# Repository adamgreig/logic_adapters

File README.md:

# Adapter PCBs for Saleae Logic

## PMOD + Picoblade

Connects a Saleae Logic or other logic analyser to a double-PMOD socket header
and to two Picoblade connectors, one 4-pin and one 7-pin.

## Cortex Debug

Connects a Saleae Logic or other logic analyser to two Cortex Debug 2x5 0.05"
connectors which are connected together, allowing analysis of signals between
a debugger and a target.

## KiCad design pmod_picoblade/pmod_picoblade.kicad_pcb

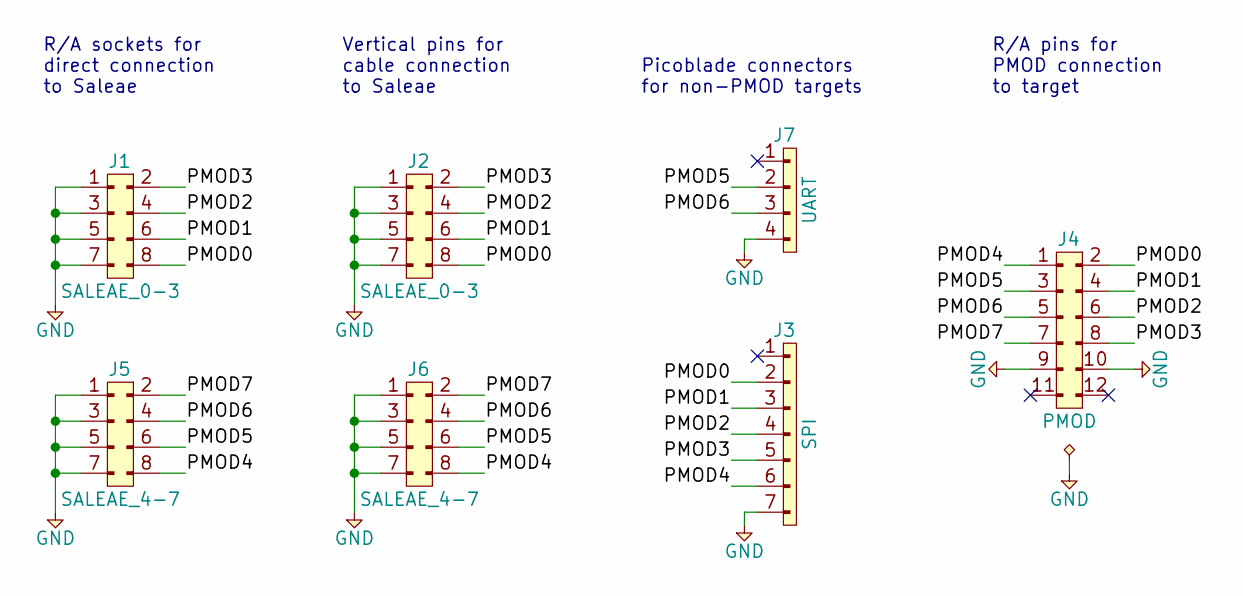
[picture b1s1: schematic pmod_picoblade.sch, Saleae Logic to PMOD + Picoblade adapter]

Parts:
J1: SALEAE_0-3; DIL-254P-08; Farnell 1668343
J2: SALEAE_0-3; DIL-254P-08; Farnell 2856692
J3: SPI; MOLEX-PICOBLADE-53398-0771; Farnell 9786368
J4: PMOD; DIL-254P-12; Farnell 2032721
J5: SALEAE_4-7; DIL-254P-08; Farnell 1668343
J6: SALEAE_4-7; DIL-254P-08; Farnell 2856692
J7: UART; MOLEX-PICOBLADE-53398-0471; Farnell 1125367

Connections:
/PMOD0: J1.8, J2.8, J3.2, J4.2
/PMOD1: J1.6, J2.6, J3.3, J4.4
/PMOD2: J1.4, J2.4, J3.4, J4.6
/PMOD3: J1.2, J2.2, J3.5, J4.8
/PMOD4: J3.6, J4.1, J5.8, J6.8
/PMOD5: J4.3, J5.6, J6.6, J7.2
/PMOD6: J4.5, J5.4, J6.4, J7.3
/PMOD7: J4.7, J5.2, J6.2
GND: J1.1, J1.3, J1.5, J1.7, J2.1, J2.3, J2.5, J2.7, J3.7, J4.9, J4.10, J5.1, J5.3, J5.5, J5.7, J6.1, J6.3, J6.5, J6.7, J7.4

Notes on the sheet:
R/A sockets for direct connection to Saleae
Vertical pins for cable connection to Saleae
Picoblade connectors for non-PMOD targets
R/A pins for PMOD connection to target

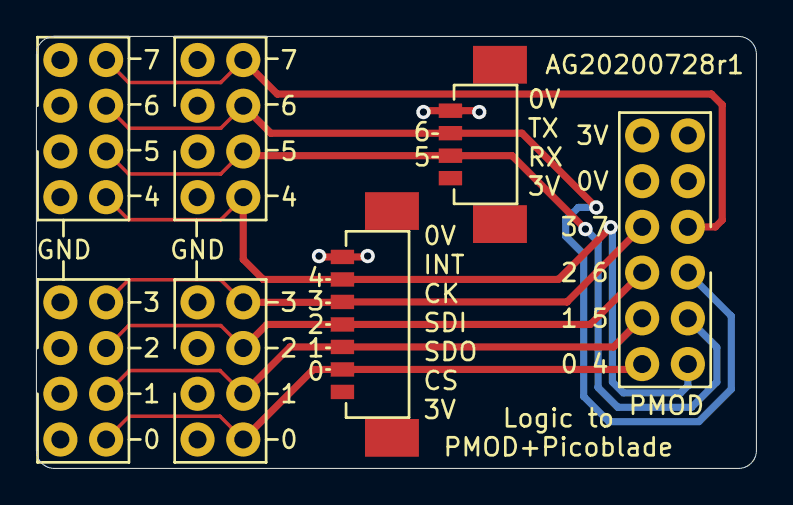
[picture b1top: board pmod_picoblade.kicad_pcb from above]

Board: 2 copper layers, 40.0 x 24.0 mm, 7 parts (0 on the bottom side), 9 nets.

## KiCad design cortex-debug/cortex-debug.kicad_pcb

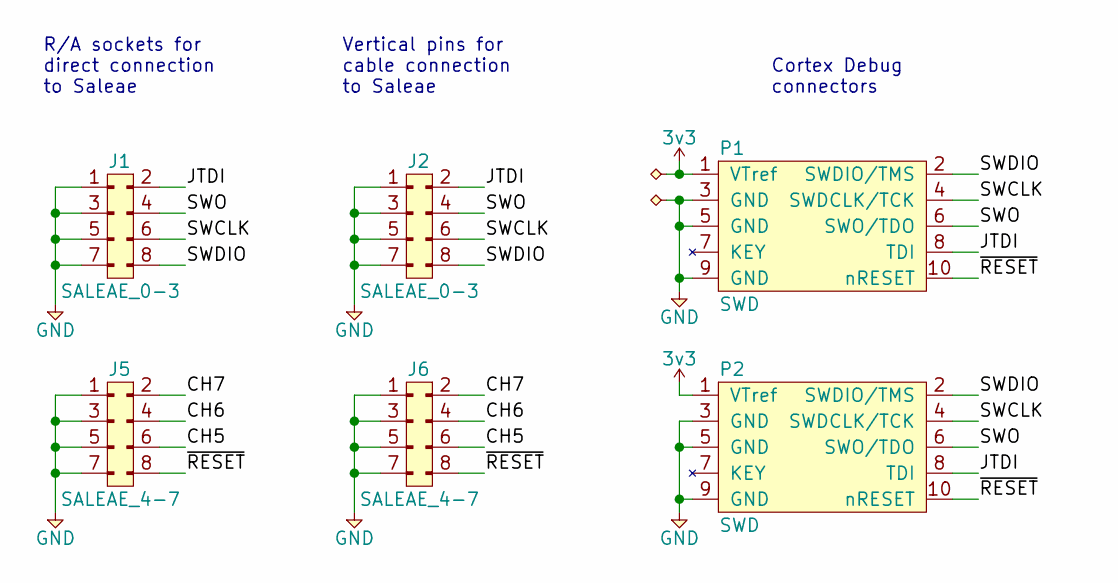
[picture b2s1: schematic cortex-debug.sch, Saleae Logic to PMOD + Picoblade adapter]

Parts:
J1: SALEAE_0-3; DIL-254P-08; Farnell 1668343
J2: SALEAE_0-3; DIL-254P-08; Farnell 2856692
J5: SALEAE_4-7; DIL-254P-08; Farnell 1668343
J6: SALEAE_4-7; DIL-254P-08; Farnell 2856692
P1, P2: SWD; FTSH-105-01-L-DV-K; Farnell 2856437

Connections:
3v3: P1.1 (VTref), P2.1 (VTref)
/CH5: J5.6, J6.6
/CH6: J5.4, J6.4
/CH7: J5.2, J6.2
/JTDI: J1.2, J2.2, P1.8 (TDI), P2.8 (TDI)
/SWCLK: J1.6, J2.6, P1.4 (SWDCLK/TCK), P2.4 (SWDCLK/TCK)
/SWDIO: J1.8, J2.8, P1.2 (SWDIO/TMS), P2.2 (SWDIO/TMS)
/SWO: J1.4, J2.4, P1.6 (SWO/TDO), P2.6 (SWO/TDO)
/~RESET: J5.8, J6.8, P1.10 (nRESET), P2.10 (nRESET)
GND: J1.1, J1.3, J1.5, J1.7, J2.1, J2.3, J2.5, J2.7, J5.1, J5.3, J5.5, J5.7, J6.1, J6.3, J6.5, J6.7, P1.3 (GND), P1.5 (GND), P1.9 (GND), P2.3 (GND), P2.5 (GND), P2.9 (GND)

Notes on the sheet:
R/A sockets for direct connection to Saleae
Vertical pins for cable connection to Saleae
Cortex Debug connectors

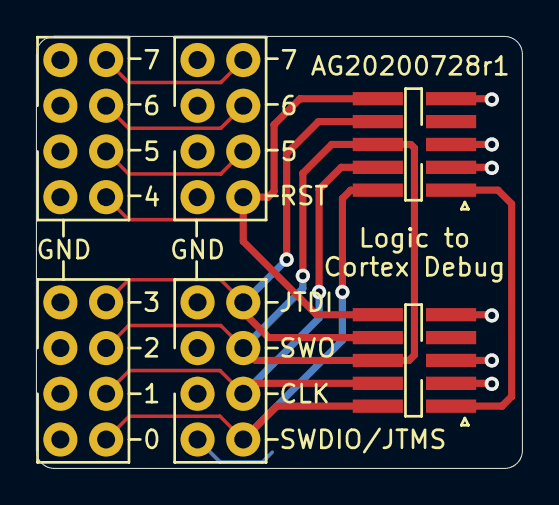
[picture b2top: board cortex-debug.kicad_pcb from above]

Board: 2 copper layers, 27.0 x 24.0 mm, 6 parts (0 on the bottom side), 10 nets.

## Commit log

2020-07-28 Initial commit with Cortex Debug and PMOD/Picoblade adapters
2020-07-28 Add images to README
2020-07-28 Update with silk date/rev code
